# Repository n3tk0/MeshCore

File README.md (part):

> **This is a fork of [meshcore-dev/MeshCore](https://github.com/meshcore-dev/MeshCore).**
> It tracks upstream and adds a Faketec v5 companion build with its own encoder-driven UI (read and write messages without a phone), a mailbox and LoRa OTA updates for repeaters (with an Android app and an nRF52 bootloader that survives power cuts), light builds of any board, plus robustness fixes to the shared MeshCore code.
> Everything below "About MeshCore" is the upstream README. For general MeshCore support, issues and contributions, please use the upstream repository.

## 🍴 What this fork adds

- [Faketec v5 companion with encoder UI](#faketec-v5-companion-with-encoder-ui): hardware, wiring, controls, writing messages, settings, build flags
- [Repeater mailbox](#repeater-mailbox-store--forward-for-direct-messages): keeps direct messages for owners who are away
- [LoRa OTA for repeaters](#lora-ota-for-repeaters-nrf52-esp32): delta updates over the air from an Android app
- [Repeater battery from an INA219](#repeater-battery-from-an-ina219) and [repeaters that look after themselves](#repeaters-that-look-after-themselves): charge counting, battery saving steps (`battsave`), self test, telemetry history
- [nRF52 bootloader for LoRa OTA](#nrf52-bootloader-for-lora-ota): staged install that survives a power cut, rollback on boards with QSPI flash
- [Fixes to upstream MeshCore](#fixes-to-upstream-meshcore): crash and hang fixes that apply to every board
- [New shared components](#new-shared-components): reusable drivers and hooks added under `src/` and `examples/companion_radio/`
- [Builds and CI](#builds-and-ci)

> Status: the Faketec v5 firmware compiles and boots with BLE. The UI has been checked in the screen simulator (`tools/ui-sim`); the latest changes (network tools, channels from the device, learned words, hardware check, buttons instead of the encoder, repeat) have not been tested on hardware yet. The repeater mailbox, LoRa OTA and the bootloader pass their unit and host tests and build in CI, but have not been tested on hardware yet either; neither have the battery steps, self test, telemetry history and the app's Health and "Update several" pages.

### Faketec v5 companion with encoder UI

A companion radio build for a Faketec v5 (rev A) board without the on-board BMS/MOSFET, with a local screen and jog-dial controls so the node can be used without a phone. User manual in Bulgarian: [docs/faketec-companion.bg.md](./docs/faketec-companion.bg.md).

| Part | Used here |
|---|---|
| MCU | Nice!Nano v2 / nRF52840 Pro Micro clone |
| Radio | Heltec HT-RA62 (SX1262) |
| Display | 128x64 SSD1306 I2C OLED (e.g. WINSTAR WEA012864) |
| Encoder | Quadrature rotary encoder with push switch (e.g. ZIPPY AN-P1S-2SP-Z), or three buttons instead (see below) |
| Buttons | User button (Back) and reset; use 2-pin switches, a 4-pin switch shorts on the SW1/SW2 footprint |
| Haptics | 3 V coin vibration motor on the board's T2 MOSFET footprint (optional) |
| Power | 1S LiPo straight from the controller's charger, battery read through a divider |

**Wiring**

| Function | Pin |
|---|---|
| Encoder A / B | P1.01 / P1.02 (common to GND) |
| Encoder push | P1.07 |
| Buttons instead of the encoder | Up P1.01, Down P1.02, Enter P1.07 (each to GND) |
| User button (Back) | P1.00 |
| OLED SDA / SCL | P1.04 / P0.11 (board I2C) |
| Vibration motor | T2 gate = P0.08, motor between B+ and drain pad J7, flyback diode across the motor |

**Controls** (Sony Ericsson CMD-Z7 style jog dial, UI in [`examples/companion_radio/ui-encoder`](./examples/companion_radio/ui-encoder))

| Input | Action |
|---|---|
| Turn | Move in lists, scroll a conversation; on standby, next status card (summary, recently heard, radio, battery, GPS) |
| Press | Open / confirm; in a conversation, reply to the selected message |
| Hold press | Quick menu (advert nearby, advert to the whole mesh, transmit on/off, Bluetooth, GPS, power off) or the actions of the current item |
| Back (BTN) | Back one level; on standby, screen off |
| Hold Back | Standby from anywhere; on standby, lock the keys (hold Back again to unlock); while the boot splash shows, CLI rescue |
| Hold Back + press 2.5 s | Power off ("Power off" shows, a double buzz confirms; does nothing while the keys are locked). To switch on, hold Back + press together ~1.5 s until it buzzes; a shorter press goes back to sleep. With USB power it starts at once. In quiet mode neither buzzes |

**Messages**

- **Messages** lists conversations (contacts and channels), newest first, with the unread count or the age of the last message. A conversation opens as a chat: every message wrapped over as many rows as it needs, my messages with their delivery icon, the age of the selected one in the title. Press replies, hold opens Reply / Resend / Delete.
- **Channels** opens a channel's conversation (or the reply picker when it has none yet). Hold on a channel: write, mute (no buzz or screen wake, except for mentions; stored in `/ui_mute`) or delete. The last row, **+ Add**, joins a `#hashtag` channel typed on the keyboard (key = first 16 bytes of `sha256("#name")`, the same as the app).
- **Message details:** hold on a message > Details shows the time, the route (direct / flood / hops), SNR and RSSI of a received message, or the attempts and state of a sent one.
- **Reply** first asks **Quick reply** or **Write**. A quick reply can be sent as is or finished on the keyboard. Replies go to where the message came from (contact or channel).
- **Sending** waits 3 s with a progress bar; Back cancels it. Direct messages are tracked: a clock until the ACK, then a check mark. Without an ACK the message is sent again automatically with the same timestamp (the recipient shows it once), the last attempt as a flood; after 3 attempts it is marked not delivered with a long vibration, and **Resend** starts a new round. Channel messages have no ACK and show as sent.
- **Mentions:** a channel message with `@name` or `@[name]` for this node vibrates and wakes the screen like a direct message.
- **Recipient list:** channels (`#`) first, then chat and room contacts, sorted by name or by last heard. Sorted by name, a row of first letters sits on top: turn left from the first entry, press, turn to a letter, press to jump to the first name with it.
- **Keyboard:** BG, EN and 123 layouts with shift (automatic capital at the start and after `. ! ?`), space, language and send keys. Turn to pick a key, press to type, Back deletes, hold opens Send / Clear / Discard. An unsent message is kept for its recipient while you write elsewhere.
- **Next word:** after a space, the word you most often sent after the previous one is suggested (pairs learned from sent messages, up to 192, ~3.5 KB in `/ui_pairs`; punctuation breaks the chain; Settings > Messages > Learned words > Clear also clears them).
- **Word prediction:** the most frequent dictionary word for what you are typing is shown after the cursor and is selected right after each letter: **press** accepts it and adds a space, turning goes back to the keys. The dictionary (6000 Bulgarian + 4000 English words, ~71 KB flash) is chosen by the script you type in; words you typed recently are suggested first. It is generated by [`ui-encoder/tools/gen_dict.py`](./examples/companion_radio/ui-encoder/tools/gen_dict.py) from [FrequencyWords](https://github.com/hermitdave/FrequencyWords) (CC-BY-SA-4.0). Learned words: words you send that the dictionary lacks (names, places, slang; 3+ letters) are learned, up to 128, stored in `/ui_words`, and suggested before dictionary words.
- **Nothing is lost before the app syncs:** every message for the phone app is written to flash as it arrives (`-D OFFLINE_QUEUE_PERSIST`, an append-only log) and leaves it only when the app has fetched it, so it survives a reset, a hang or a flat battery (up to 256 messages; when full, the oldest channel messages go first). The device's own history (last 24) is not cleared by a sync; it is written within 10 minutes of a change, at power off and before an update. Messages sent from the device do not appear in the phone app's history.

- **Quiet hours:** Settings > Messages > Quiet hours (off, 22–07, 23–07, 00–07, 22–06, 23–06): in those hours channel messages neither wake the screen nor vibrate; direct messages and mentions still do. Only with a valid clock (from the app or an advert); without one it is off.
- **"I'm back":** after a power-on or a wake from sleep/hibernate, and when a repeater is heard again after 10+ minutes without one (its advert, or any flood packet it passes on, so a node that stays near a repeater does not do it every hour), the companion sends one zero-hop advert by itself (at most once in 10 minutes, only while transmit is on), so a repeater's mailbox hands over at once (`-D BACK_ADVERT`). When the mailbox delivers, the screen shows "Mailbox: N msgs".
- **Battery:** the battery card shows the voltage and the time left (e.g. `3.8V ~18h`), from how fast the percentage fell over the last hours; the next card is a 24-hour graph of the battery with its low–high %. The history (every 10 minutes for 24 h, every hour for a week, `-D TELEMETRY_HISTORY`) is kept in `/tele_hist` and the app reads it (BLE command 121).

**Network** (Menu > Network)

- **Nearby:** a zero-hop discover request; the repeaters that answer in 10 s, strongest first. A repeater shows how well it hears us (↑) and we hear it (↓), and starts a trace or range test to it. Hold searches again.
- **Trace:** from a contact (hold > Trace) or a nearby repeater: a TRACE packet there and back through the repeaters of its path, with the SNR at each hop and the round-trip time.
- **Airtime:** transmit time in the last hour against the EU 868 MHz 10% duty cycle, total TX time, packets sent / received / errors, noise floor, last SNR and RSSI.
- **Range test:** a trace to the chosen repeater or contact every 15 / 30 / 60 / 120 s, a buzz for each answer (a different one for a miss), the last results with SNR there and back. Keeps running with the screen off until stopped (an icon in the standby status row shows it); stops if transmit is switched off.

**Settings** (Menu > Settings, saved in prefs)

| Group | Settings |
|---|---|
| Display | menu font and text font size (large / medium / small / tiny), screen timeout (15 s – 5 min), brightness, page dots |
| Hardware | encoder direction, encoder steps per detent (2 / 4; hidden with buttons), vibration, keyboard jump to the likely next letter, key lock (by hand / automatic when the screen goes off), input test, vibration test, screen test, readings (battery raw/ADC, USB, reset reason, noise floor, uptime) |
| Messages | alerts (without phone / always / never), wake the screen for (direct and mentions / all / never), quiet hours, confirm deletes, contacts sort, 10 quick replies (stored in `/ui_quick`), learned words (count, clear) |
| Radio | transmit on/off, TX power, antenna question (after a new battery / every boot / never), preset (EU/UK Narrow, EU/UK Deprecated; anything else shows as custom), repeater |
| System | node name (an advert with the new name is offered; the Bluetooth name changes after a restart), language BG / EN, time zone, EU summer time, battery calibration, about, CLI rescue, firmware update over USB (UF2 drive) or BLE (DFU) |

**Buttons instead of the encoder:** Up on P1.01, Down on P1.02 and Enter on P1.07, each to GND. The firmware is the same: after a new battery, the first turn or press at the antenna question shows which is fitted, and that is remembered across restarts and power off. A held button repeats. A wrong guess fixes itself: two full encoder clicks in one direction within 1 s switch to the encoder, two presses of one button within 2 s switch to buttons.

**Repeater (emergency only):** Settings > Radio > Repeater (or the phone app) makes the companion repeat other nodes' packets. It loads the mesh and the battery, so it asks "Emergency only! Turn on?" first, and a tower icon shows in the status row while it is on. It is allowed on 433.000, 869.495, 869.618 (EU/UK Narrow) and 918.000 MHz (`-D ALLOWED_REPEAT_FREQ_RANGE` in the Faketec ini); while it is on, a preset on another frequency is refused.

**Battery calibration:** Settings > System > Battery shows the measured voltage; set it to what a multimeter shows at the battery and the divider factor is saved in prefs. The shown value is averaged, and the node powers off only after three low readings in a row, so a transmit pulse does not switch it off.

**Watchdog:** the nRF52 hardware watchdog (30 s, `-D WATCHDOG_SECONDS`) restarts a node whose main loop hangs, e.g. on a stuck I2C bus, so the low-battery cutoff keeps working. The bootloader feeds it, so DFU and UF2 updates are not affected.

**Build flags** (in [`variants/faketec_v5/platformio.ini`](./variants/faketec_v5/platformio.ini))

- `-D DISPLAY_CYRILLIC`: Cyrillic 5x8 font for the SSD1306.
- `-D PIN_VIBRATION`, `-D VIBRATION_PWM=190`: haptic patterns (key click, confirm, channel / direct message, power off); PWM keeps the motor near 3.1 V on a full LiPo. Remove to build without a motor.
- `-D AUTO_SHUTDOWN_MILLIVOLTS=3300`: there is no BMS, so the node hibernates below this voltage. Calibrate in Settings > System > Battery (or set `-D ADC_MULTIPLIER` for your divider).
- `-D ENCODER_STEPS_PER_DETENT=2`, `-D ENCODER_REVERSE=true`: build defaults for the encoder; both can also be changed in Settings.
- `-D DISABLE_RTC_AUTODISCOVERY`, `-D DISABLE_ENV_SENSORS`: skip the RTC probes and the sensor scan when none are fitted (a faster boot; a bad I2C bus no longer hangs it, see below).
- `-D ALLOWED_REPEAT_FREQ_RANGE=...`: the frequencies where the repeater setting may be turned on (upstream allows 433.000, 869.495 and 918.000 MHz; this build adds 869.618).

Build with PlatformIO, e.g. `pio run -e Faketec_v5_companion_radio_ble` (or `_usb`), then flash the UF2 by double-tapping reset and copying it to the bootloader drive.

<!-- release-notes:repeater:start (tools/repeater-release-notes.sh puts the text from here to the end marker in the repeater release) -->
### Repeater mailbox (store & forward for direct messages)

Every repeater built from this fork (`-D NO_MAILBOX` leaves it out) can keep direct messages for up to 4 owner companions while they are away, and hand them over when the owner is heard again with no hop between. Nothing is flooded: messages are kept from traffic the repeater hears anyway, and handed over as zero-hop packets that nobody repeats.

- **What is kept:** only `TXT_MSG` packets addressed to an owner (by the first public key byte, the only one in the packet), still encrypted to the owner; the repeater cannot read them. Channel messages, adverts and messages sent with no hop (the owner is next to the sender, or another mailbox is handing over) are not kept. Off until `mailbox learn` or `mailbox on`. Up to 64 messages (8 on STM32) in flash (`/mailbox`), so they survive a restart; older than `ttl` hours are dropped (after a restart without a clock, the age counts from the restart); when full, the oldest goes.
- **Only while away:** an owner heard with no hop in the last `away` minutes (its signed advert, or its ACK to a message this mailbox handed over; a packet that only carries the first key byte does not count, since a neighbour may share it) is present, and nothing is kept for it. A flood message the owner answered with a PATH reply in the next 2 minutes is dropped as delivered. A sender's automatic retries (same sender, same length, within 30 s) are kept once.
- **Hand-over:** on any zero-hop packet from the owner (an advert, a message, a request, a PATH; the Faketec sends an advert by itself when it comes back), the kept messages go out one every 2.5 s as zero-hop direct packets. A packet other than an advert carries only the first key byte, which other nodes can share, so then one message goes at a time and the next only after the owner's ACK was heard (at most one such try a minute); a signed advert arriving meanwhile lets the rest go without waiting; only an ACK sent to this repeater counts. If the owner's ACK goes out through another repeater, this one does not hear it: the message stays and goes again with the owner's next packet, and the companion shows it once (a repeat, never a loss). The owner ACKs them as usual; a sender that is still on the mesh gets the late ACK, and the Faketec UI turns its "not delivered" into delivered.
- **Shown once:** the companion firmware drops a direct message it already showed (same sender and timestamp, last 32), so a kept copy or a retry is not shown twice; the sender still gets its ACK.
- **Count:** the number of kept messages is in `selftest` (`mail=N`) and on the app's Health page.
- **CLI** (serial or remote admin): `mailbox` (state), `mailbox on|off`, `mailbox learn` (the next companion advert with no hop in 2 minutes becomes an owner), `mailbox add <64-hex key>`, `mailbox del <key prefix>`, `mailbox list`, `mailbox ttl <hours>` (default 72), `mailbox away <minutes>` (default 10), `mailbox clear`.
- **App:** the Android app's Mailbox card (repeater Tools) shows the recipients by contact name, adds the connected companion with one tap ("Add me", its own key, no advert needed), a contact or a pasted key, and changes on/off, `ttl`, `away`; the repeater lists show ✉ N ("you too") from the last read.

### LoRa OTA for repeaters (nRF52, ESP32)

- **How:** the Android app in [`android/`](./android) (user guide with screenshots in Bulgarian: [docs/android-app.bg.md](./docs/android-app.bg.md)) makes a delta from the firmware the repeater runs to the new one and sends it through your companion, only with no hop, on a side channel (default 869.470 MHz / 125 kHz / SF7) so the main channel keeps working.
- **Off by default:** run `set ota on` in the repeater's console first (`set ota off` turns it off again, `ota status` shows it). `ota sha` prints the SHA-256 and size of the running image (kept in `/ota_sha`, so it is hashed once per build); the app finds the matching firmware in the releases with it, and the commit in the ident (`<version> <date> <commit>|<board>`) tells which build it is.
- **Cut short:** the repeater goes back to its normal channel and keeps its progress for 30 minutes; the same update in the app continues where it stopped.
- **Time on air:** the app keeps to 10 % of each hour; a bigger delta waits for the next part of the hour on the normal channel.
- **nRF52 storage:** the new image goes to the free internal flash after the running one, then is copied over it just before the restart. Repeaters with a QSPI flash (Xiao nRF52840, Ikoka Stick/Nano/Handheld, T-Echo, ThinkNode M1/M6, Wio Tracker L1 and L1 1W, SenseCAP Solar; `-D QSPI_STORAGE`) keep it there instead, together with the mailbox (a ring of 24 slots) and a copy of the running image for rollback (832 KB each, more than the whole app area). Boards where the old and the new image do not fit together (e.g. RAK4631, about 460 KB) update **in place**: the repeater keeps the delta and the end of the image, and makes the start again in RAM just before the copy. The app shows a big warning for it.
- **Our bootloader (nRF52):** with [our bootloader](#nrf52-bootloader-for-lora-ota) the final copy survives a power cut, and boards with QSPI flash get rollback.
- **Power cut on nRF52 without it:** during the final copy (about 20 s) a power cut leaves the repeater in the bootloader with no firmware; it has to be updated on site (USB or BLE DFU). The stock bootloader then at least checks the image's CRC at every start. ESP32 has two app slots and is not at risk.
- **Low battery:** the final copy waits while the repeater runs on a battery below 3.7 V (`-D OTA_MIN_BATT_MV`); the update is paused and the app offers to continue.
- **Watchdog on nRF52 repeaters:** 60 s (`-D REPEATER_WATCHDOG_SECS`, 0 = off). It cannot be stopped: after loading firmware that does not feed it, press RST once.
- **New firmware must prove its radio:** a new image (ESP32, or nRF52 with rollback) is confirmed by an admin login, or once it has sent and received a packet within 10 minutes (it sends an advert at 5 minutes if it has not sent anything). With nothing heard by 60 minutes it is still confirmed when its noise floor is sane (-140..-60 dBm, a quiet area), otherwise it rolls back. `ota rollback` does it by hand.
- **Where the firmware comes from:** the app offers three sources for both an update over LoRa and a flash over Bluetooth / Wi-Fi: **Releases** (ours with `ota-manifest.json`, and for a flash also stock MeshCore from meshcore-dev), **New build** (runs [Build Firmware for Boards](#builds-and-ci) on GitHub with the board picked from the device and the workflow's own boxes, then downloads the run's artifact and checks it against its `.ota.json`) and **File**. A build needs a fine-grained GitHub token for this repository with *Actions: Read and write* and *Contents: Read*; it is kept on the phone only, encrypted with an Android Keystore key. The app follows the run in the background and notifies when it is done. For a group: Actions > Build LoRa OTA Android App > Run workflow with *group APK* builds a second APK with the token from the secret `LORAOTA_GITHUB_TOKEN` (XOR-ed, not readable as text, but anyone who takes the APK apart can get it), only as an artifact kept 3 days, never in a release.
- **Flash from a file:** `.zip` (DFU package), `.bin` (Wi-Fi, ESP32) or `.uf2`; a `.uf2` is turned into a DFU `.zip` in the app (application only, any SoftDevice), so the same file as for the USB drive works over Bluetooth. A bootloader or SoftDevice `.uf2` is refused.
- **Bluetooth flash log:** the flash screen shows the DFU library's log while it runs and keeps it after an error, with a Copy button. A repeater is flashed without a bond and the app looks for its bootloader by scanning (the Adafruit bootloader advertises on the address + 1 after a jump from the app).
- **4-tab repeater workspace (`Overview` · `Health` · `Firmware` · `Tools`):**
  - **Overview:** battery status (with chemistry selection and INA219/BQ25798 current), **Quick Actions** (1-tap UTC clock sync from the phone, flood advert, refresh, reboot confirmation, and a **5x Ping Link Range Test** reporting delivery % and min/avg/max RTT ms), and **Neighbors** (resolves 8-hex prefixes to contact names, shows color-coded SNR badges, supports `neighbor.remove`, and calculates **Haversine distance & compass bearing** such as `14.2 km SE (138°)` when coordinates are known).
  - **Health:** summary card, `selftest` in words, lazy on-demand 24 h / week telemetry charts with **CSV export**, past checks, and collapsible `battsave` / battery capacity configuration.
  - **Firmware:** LoRa delta OTA and Bluetooth DFU / Wi-Fi OTA with a sticky bottom action bar.
  - **Tools:** interactive **CLI console** (also available locally for the companion; supports quick chips, custom persistent snippets with secret-command blocking, history, `get`/`set` autocomplete, RTT badges, dangerous-command confirmation, stock companion fire-and-forget mode, and redacted copy/share), **Visual Settings Editor** (writes only modified keys, validates ranges, fills `lat`/`lon` from **phone GPS** in 1 tap, supports **reusable Config Profiles**, and embeds a **live LoRa Airtime / Bitrate / Sensitivity / 10% duty-cycle calculator**), safe temporary radio test (**`tempradio`** with auto-revert), and Backup / Restore.
- **Fleet management & Batch Health Sweep:** pin important repeaters to the top, filter by `All | Direct | Issues | Pinned`, see latest battery % and health status dots in the repeater list, and run **Fleet Health Sweep** to sequentially log in to selected repeaters, run `selftest` (with optional batch UTC clock sync), store results, retry failed nodes, and share a text report.
- **4-tab Offline Hub (`Health` · `Backups` · `Firmware` · `Audit & Mesh`):** works without a Bluetooth connection:
  - **Health & Backups:** search saved health checks and backups, **import external `.json` backup files**, **compare any two backups (Diff)**, or save a repeater backup as a reusable config profile.
  - **Offline Firmware Hub:** pre-cache release firmwares (`Prepare for field` board picker with search and role filters), trigger custom GitHub builds for **any device role (`Repeater`, `Companion`, or `Room server`)**, export `.bin` / DFU `.zip` files, or **Flash directly (`Flash`)** over BLE DFU (`*_OTA` / `DfuTarg`) or ESP32 Wi-Fi (`MeshCore-OTA`) in the field without a companion.
  - **Audit & Mesh Intelligence:** inspects **Offline LoRa OTA Delta Readiness** (whether both base and target `.bin` files are cached for each known repeater), runs an **Automated Fleet Configuration & Security Audit** (radio mismatch, `lat=0, lon=0`, `repeat=off`, open guest write access, low battery), and builds a **Mesh Link Topology & SNR Asymmetry Matrix** flagging bidirectional links with `>= 6.0 dB` asymmetry.
- **Security, BLE Auto-Reconnect & Full Workspace Archive:** repeater admin passwords are encrypted with Android Keystore AES/GCM (`PasswordStore`); unexpected BLE disconnects automatically retry twice before dropping the session; `Settings` includes in-app GitHub self-update (`AppUpdater`), redacted diagnostic report sharing, and **Encrypted Full Workspace Archive** export/import (`PBKDF2-HMAC-SHA256` + `AES-256-GCM`) bundling all backups, health history, repeater passwords, pins, CLI snippets, config profiles, and observed neighbor topology.
- **Several repeaters at once:** "Update several repeaters" picks a release and the repeaters with a kept password (the others are shown greyed: log in to them once; those with hops are marked as skipped unless the route becomes direct). A confirmation lists the repeaters and the release. It then logs in, backs up and updates them one after another (no-hop routes first), keeps to the shared airtime limit, saves the queue after each one so it goes on after an interruption, keeps running with the screen off (one notification for the whole queue), marks a repeater that fails (a broken download, an odd answer) and goes on with the next (only a lost companion stops it), and ends with a report (updated / already up to date / skipped and why / failed). A repeater that needs an in-place copy is skipped (do it by hand).
- **APK signing:** CI signs with the key from the secrets `LORAOTA_KEYSTORE_BASE64`, `LORAOTA_KEYSTORE_PASSWORD`, `LORAOTA_KEY_ALIAS`, `LORAOTA_KEY_PASSWORD` (a debug key when they are not set).

### Repeater battery from an INA219

With an INA219 in the battery line (the battery on Vin+, the load and the charger on Vin-), the repeater takes the battery from it instead of the board's ADC: bus voltage plus the drop over the shunt. It is used in the status, telemetry channel 1, the `power` command and the battery check before a LoRa OTA install. The INA219 channel also carries the current with its sign as an analog input (Cayenne LPP current has no sign): negative while charging, positive while discharging. Without an INA219, or after it was turned off for I2C errors (see `i2c` below), the board's own reading is used.

### INA226 battery and the xiao-solar-lite v0.6 board

An INA226 at 0x44 is plain telemetry on every board. With `-D INA226_BATTERY=1` it is the battery, like the INA219 above (battery on Vin+, load and charger on Vin-, 100 mOhm shunt): the voltage, the charge counting and the percentage in telemetry come from it, the board's ADC is not used, and when a read fails or the sensor is turned off the last good value is kept (unknown, 0, until the first good read; `battsave` and the OTA check treat that as no reading). A second INA226 at 0x45 (found by its manufacturer ID) is a second telemetry channel. `-D INA226_LOW_POWER=1` reads them in triggered mode with 16 averages (~35 ms, the chip rests at ~2 uA in between).

`Xiao_nrf52_solar_repeater` is one XIAO nRF52840 + Wio-SX1262 repeater for every XIAO solar board, found at boot (`solar` command: BQ25798 lite v0.5, CN3791 lite v0.6, MSPM0 xiao-solar / smart-mppt; `Xiao_nrf52_solar_lite_repeater` is the same build under the old name). On the CN3791 (former ultralite) board: a CN3791 buck MPPT charger, the battery INA226 on 0x44 and the solar input INA226 on 0x45 (SCL D6 / SDA D7); the XIAO's own battery pad is not connected. D0 drives the charger's panel voltage set-point through a PWM (`-D SOLAR_MPPT_PWM_PIN=D0`); `charger` takes the same words as on a BQ25798 (`vin mppt|off|<mV>`, `ichg` 100..600 mA as a software limit through the set-point, `scan`, `cutoff` = the battsave off step; `mppt` is short for `charger vin`), see the [docs](./docs/cli_commands.md#solar-panel-set-point---mppt-repeater-xiao-solar-lite-v06). Not hardware-tested yet.

### xiao-solar-lite charger (BQ25798)

All solar boards (commands and capabilities per board and version): [docs/solar-boards.bg.md](./docs/solar-boards.bg.md).

`Xiao_nrf52_solar_lite_repeater` is the XIAO nRF52840 + Wio-SX1262 repeater for the xiao-solar-lite board (a small BQ25798 solar charger for XIAO + Wio-SX1262; private repo Meshcore-hardware): BQ25798 on I2C (0x6B, SCL D6 / SDA D7), its ~CE on D0 (so D0 is no button here). The firmware turns the charger's watchdog off and keeps its setup (Li-ion 4.20 V or LiFePO4 3.60 V, 1 A, MPPT on again every morning, TS ignored unless an NTC is fitted, ship FET), reads battery and panel voltage and current from the charger's ADC every 10 s for status, telemetry, charge counting and `battsave`, and puts the board into shutdown mode when the battery is empty and there is no sun (only the panel wakes it). `charger` in the CLI ([docs](./docs/cli_commands.md#charger---bq25798-on-xiao-solar-lite-repeater-only-xiao_nrf52_solar_lite_repeater)). The XIAO ESP32-C3 is not supported on this board (D0 is a strapping pin there). Not hardware-tested yet.

### Repeaters that look after themselves

- **Charge counting (INA219):** with the current sensor the repeater counts the charge in and out: a real %, hours left at the 6-hour average, and today's / yesterday's mAh in and out. The capacity is learnt from a full charge (4.15 V with only a trickle going in) down to empty (3.3 V), or set with `battery capacity <mAh>`. In telemetry, `selftest` and `battery`.
- **Power steps:** below 3.6 V adverts go half as often and the mailbox stops writing to flash; below 3.45 V no LoRa OTA and no mailbox; the 'off' step (radio off, only battery checks: ESP32 deep sleep 30 min and back to sleep at once on waking if the battery is still under off + 150 mV; nRF52 every 10 min) is not on by default, because a wrongly calibrated ADC would take a remote repeater off the air; `battsave 3600 3450 3300` (or the app's battery card) turns it on. It restarts the node when the battery is 150 mV above it or on external power; an ESP32 woken by its timer checks the battery before the radio starts (with an INA219, right after the sensors, and puts the radio back to sleep) and sleeps again while it is still low. 3 readings in a row decide a step down, 100 mV above the limit a step up. `battsave` shows and sets it. It is not upstream's `powersaving` (the MCU sleeps between packets while the radio listens); both can be on.
- **Sensors come back:** a sensor turned off after I2C errors is tried again after 10 minutes, 1 hour, then every 6 hours (after a day without errors a new drop-out starts again from 10 minutes), and set up again when it answers (a lost supply resets its registers); `i2c` shows how often it dropped out.
- **Self test:** `selftest` gives one line for the app's Health page and for people (see [docs](./docs/cli_commands.md#self-test)).
- **Telemetry history:** every 10 minutes for 24 h and every hour for a week (battery, current, temperature, humidity, pressure, noise, packets, airtime), kept in `/tele_hist` (saved every hour), read by the app with request `0x41` (not on STM32); each reply also says which values the node has, so the app offers only those, and a value it does not measure costs one short reply. After a restart without a clock the time goes on from the last known one (the time the node was off shows as a gap once the clock is set).

### nRF52 bootloader for LoRa OTA

[`bootloader/`](./bootloader) is the [OTAFIX bootloader](https://github.com/oltaco/Adafruit_nRF52_Bootloader_OTAFIX) (pinned commit) with one addition, a **staged install**. Details, layout and build: [bootloader/README.md](./bootloader/README.md).

- **What it changes:** the repeater puts the whole new image where the copy does not touch it (the QSPI flash, or the internal flash after the running image), writes a small record in the bootloader settings page and restarts. The bootloader checks the image (CRC-32), copies it, checks the result and marks the record. The source is never written, so a power cut during the copy only makes it start again.
- **Rollback (boards with QSPI flash):** the running image is also kept in the QSPI flash and the new one runs on trial. It is confirmed by an admin login, an INFO from the LoRa OTA app or 10 minutes of uptime; after 3 restarts without that (a crash, or a hang caught by the watchdog) the bootloader copies the old image back. `ota rollback` on the repeater does it by hand.
- **Old bootloader:** firmware from this fork still updates the old way (RAM copy), and now also stores the image's CRC16, which the stock bootloader checks at every start.

| What a repeater gets | Boards |
|---|---|
| staged install + rollback (`-D QSPI_STORAGE` in the repeater env) | Xiao nRF52840, Ikoka Stick / Nano / Handheld (Xiao bootloader), LilyGo T-Echo, ThinkNode M1, ThinkNode M6, Wio Tracker L1 and L1 1W, SenseCAP Solar P1 |
| staged install, normal build (image up to 396 KB) | ProMicro / Faketec, T1000-E, ThinkNode M3, Heltec T114 without display, RAK WisMesh Tag, Minewsemi ME25LS01 |
| staged install only with a light build (`build-boards.yml`, about 310-336 KB) | RAK4631, RAK3401, Heltec T114 with display, Heltec T096, Heltec T1 |

Every repeater board and which bootloader it should use (and why the others keep the stock one): [bootloader/README.md](./bootloader/README.md#every-repeater-board). Bigger images still update over LoRa, the old way. T114 and T1000-E have QSPI flash, but its pins are not known yet; RAK boards have at most 1 MB of QSPI flash, too small for the layout.

**Install** (once per node): get `update-<board>_bootloader-…-mcota1_nosd.uf2` from a `bootloader-v*` release or the Build Bootloader workflow's artifacts, double-tap RST and copy it to the drive. `INFO_UF2.TXT` on the drive names your board; on a Xiao pick the Sense file only if it says `SeeedXiaoSense`. The firmware finds the new bootloader by itself; nothing else needs changing.

### Fixes to upstream MeshCore

These are in shared code and apply to every board.

- **Crash on short frames from the app:** `CMD_SEND_CHANNEL_TXT_MSG` shorter than its 7-byte header made the text length negative and `sendGroupMessage()` copied ~4 GB. All command handlers that read fixed-size fields now check the frame length first, instead of reading stale bytes from the previous frame; `REBOOT` / `FACTORY_RESET` could previously match text left over from an earlier frame. `SEND_RAW_DATA` path length and `SET_DEFAULT_FLOOD_SCOPE` name scan are bounded.
- **Malformed radio packets:** a `PAYLOAD_TYPE_PATH` whose path runs past the data no longer underflows the extra length and overruns `out_frame`; `TRACE` packets need tag, auth and flags before the hop offset is computed; contact responses are clamped to the frame size.
- **Invalid path lengths:** an invalid `out_path_len` from the app or from `/contacts3` is treated as unknown (flood) instead of producing malformed direct packets.
- **nRF52 BLE RX race:** the RX queue was shifted in `loop()` while the Bluefruit callback appended to it without locking, so frames could be lost or duplicated. It is now a single-producer / single-consumer ring; connect / disconnect request a flush that `loop()` performs.
- **Atomic saves on nRF52:** contacts, channels and prefs are written to a temp file and renamed, so a reset or brown-out during a save no longer corrupts them (falls back to an in-place write when the filesystem has no room for a second copy).
- **Hang on the I2C bus (nRF52):** the Adafruit Wire driver waits on the TWIM with no timeout and reads an error left by an earlier transfer as its own, so a loose cable or a module holding a line could stop a node at boot or in a sensor read. [`arch/nrf52/libs/nrf52_wire`](./arch/nrf52/libs/nrf52_wire) is that driver with a 50 ms timeout on every wait (`-D WIRE_TIMEOUT_MS`), a reset of the TWIM, bus recovery (9 SCL clocks and a STOP), stale events cleared before each transfer and error counters; it replaces the framework's Wire on every nRF52 build, so sensor libraries and displays get the timeouts too. A device that times out at boot, or whose reads fail 3 times in a row, is turned off until a reboot and the others go on (it keeps its telemetry channel). The CLI command `i2c` lists what was found and what was turned off and why ([docs](./docs/cli_commands.md#show-the-i2c-devices-and-the-ones-turned-off)). The flags `-D DISABLE_RTC_AUTODISCOVERY` and `-D DISABLE_ENV_SENSORS` still skip the RTC probes and the sensor scan.
- **Display left on after power-off:** `ui-new` and `ui-tiny` put a non-e-ink display to sleep before SYSTEMOFF, so the OLED no longer drains the battery after hibernate or low-battery shutdown.
- **STM32 builds:** `[stm32_base]` pins the STM32duino framework, because the new 3.0 release breaks RadioLib's Arduino HAL and drops `ltoa()`.

<!-- release-notes:repeater:end -->
### New shared components

- `src/helpers/ui/QuadratureRotaryInput`: interrupt-driven quadrature decoder with 2 or 4 transitions per detent, resync at the rest position, runtime direction and steps; ISR-safe on ESP32.
- `src/helpers/ui/SSD1306Display` + `CyrillicFont5x8.h`: UTF-8 Cyrillic rendering (`-D DISPLAY_CYRILLIC`); characters the font cannot draw show as a block.
- `src/helpers/ui/GenericVibration`: PWM drive and multi-pulse patterns.
- `src/helpers/ui/MomentaryButton::setDebounce()`: debounce without the multi-click delay, so presses register at once.
- `AbstractUITask::msgSource()`: optional hook telling a UI whether the next message came from a contact or a channel (no-op for the other UIs).
- `DataStore::loadSmallFile()` / `saveSmallFile()`: small UI-owned files with the same atomic save.
- `src/helpers/I2CHealth`: I2C probe with a timeout result, the error counters and the list `i2c` shows.
- `SensorManager::getBatteryMilliVolts()`: a battery from a sensor (the INA219), 0 when there is none.

### Builds and CI

- [`.github/workflows/build-boards.yml`](./.github/workflows/build-boards.yml) builds chosen boards by hand (Actions > Build Firmware for Boards > Run workflow): pick a repeater / companion / room server from the drop-downs, type more env names, or add a whole group (a filter such as `Xiao` narrows only the group; picked boards are always built). Light by default: RTC, sensors, GPS, screen driver and debug logs stay out unless ticked (without the display box the screen is a no-op but buttons, LED and buzzer keep working; boards that start their GPS in their own code keep it) (mailbox and LoRa OTA stay in unless unticked), and such files get `-lite` after the board name; [`tools/lite-flags.sh`](./tools/lite-flags.sh) gives the same flags for a local build (a board with a sensor built in marks it in its env `build_flags`, e.g. `-D LITE_KEEP_INA260 -D LITE_KEEP_MLX90614`: that sensor is never dropped and the I2C scan stays on; `ENV_INCLUDE_BQ25798` counts too). After new boards arrive, `bash tools/gen-board-choices.sh` refreshes the drop-downs. Files go to the run's artifacts, and optionally to a GitHub pre-release. The LoRa OTA app can start it too (input `request_id`, which names the run so the app finds it).
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
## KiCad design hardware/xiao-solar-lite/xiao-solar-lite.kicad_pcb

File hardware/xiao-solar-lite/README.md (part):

# xiao-solar-lite: solar charger layer for XIAO + Wio-SX1262

The power part of [`../xiao-solar`](../xiao-solar) as the third layer of the standard
XIAO nRF52840 + Wio-SX1262 sandwich: this board at the bottom, Wio in the middle, XIAO on top
(USB and buttons stay reachable). Solar input, BQ25798 MPPT buck-boost charger, optional NTC,
ship FET, and DW01A + HJ8205 battery protection (BMS).
25 × 70.3 mm, 2 layers, all SMD parts on the top side (JLC assembly), no mounting holes.

The stack sits over the 14 XIAO holes at the USB end; since v0.5 nothing at all is under it (no SMD part inside the U3 outline, only tracks and vias): the
charger, the ideal diode and the BMS sit below the stack, 3 mm or more away from the header pins. Long pin headers go through all three boards.

Status v0.5: schematic, routed PCB, Gerber, JLC BOM/CPL. Not built or tested.

v0.3 (review 2026-10-29): charger zone redone after the BQ25798 layout guide (SLUSDV2C 8.4.1):
PMID, SYS, VBUS and BAT are copper areas, SW1/SW2 run short and wide to the inductor, the 100 nF
PMID/SYS caps sit at the pins, BTST/REGN/GND leave through vias under the package. Cap counts as
TI recommends (VBUS 2, PMID 3, SYS 5, BAT 2 × 10 µF), so the board grew by 4 mm. Small parts get
thermal spokes to GND (easier hand rework), the charger power caps stay solid.
Every layer change on a power net has two vias (no single-via hot spot), and no via sits in a pad.

v0.4 (2026-10-30, Argon review + v0.4 proposals, shared with the main board):
- Charger per TI 8.4.1: 0402 100 nF right over the PMID–GND(27) and SYS–GND(27) pins on top,
  SW1/SW2 drop through 3 vias each under the IC to short B.Cu copper to L1, pin 27 to several vias.
  L1 is a molded **MWSA0402S-2R2MT** (Isat 4 A, DCR ≤ 58 mΩ, less stray field near the radio).
- **JP3** solder jumper across the ship FET Q2: closed = no ship FET, for LiFePO4 (with the ship
  FET the BQ25798 starts above 3.40 V and stops below 3.20 V; without it 2.6 / 2.4 V).
- **DW01A + HJ8205 BMS** (`U2`, `Q3`, `R9`, `R10`, `C19`) on the low side of the battery, matching
  the main board (`2.4 V / 4.3 V` backup protection).
- **Optional NTC** (`J3` + `R2/R3 = 5.1k/30k`), matching the main board: firmware sets `TS_IGNORE`
  by default when no NTC is fitted; CLI command enables the 0–60 °C NTC window.
- D5 was an **LM66100** ideal diode (~30 mV drop instead of ~0.3 V), replaced in v0.5 (see below); D1 is **SS54**.
- DFM: no vias in SMD courtyards except the tented ones under U1, 4 mm GND via grid + 3 mm edge
  fence, GND vias at caps and signal vias, B.Cu kept whole under the charger, teardrops,
  3 fiducials, test points VBUS/PMID/SYS/BAT/GND/3V3/SCL/SDA, parts ≥ 1 mm from the edge,
  silk ≥ 0.8 mm without overlaps (some refs in tight spots are hidden, they stay on F.Fab).
- Rotations in the CPL: U1, U2, Q2, D1, D3, D4 agree with JLC's footprints. Q3 (+270, the HJ8205 has its
  pins in two columns in JLC's footprint) and the SOT-23 parts (+180) are confirmed by JLC's DFM view
  (2026-11-13); D5 is gone.

v0.5 (2026-11-13):
- **Discrete ideal diode instead of the LM66100** (same circuit as the xiao-solar main board, no extended-part
  fee): `Q5` AO3401A (C15127) in the SYS to VOUT path, mirror `Q6` / `Q7` MMBT3906 (C7420354),
  `R30` 1M and `R31` 470k (0603, C22935 / C23178). Q5, Q6, Q7, R30, R31 and C20 sit in one column
  right of the SYS caps (x = 22.2 mm, y = 38 to 57 mm); SYS reaches the Q5 drain over a short 0.8 mm stub,
  VOUT leaves the source on a 0.8 mm track along the right edge to U3 pin 14 (about 45 mm). The
  mirror lines are hand-routed 0.25 mm tracks on F.Cu, no vias.
- **All SMD pads are at least 3.0 mm (copper to copper) from every pin of the headers** (U3, J1, J3, J4, J5),
  as JLC's DFM asked on the main board, and **nothing is under the XIAO / Wio stack** (no courtyard overlaps
  U3). The board is now **25 × 65 mm** (was 23 × 62; later 66.3 mm for the connector row, see below): the extra 2 mm of width hold the ideal diode column,
  R11 / R12 (I2C pull-ups, right of the charger top) and the VOUT track; the stack sits against the left edge
  (U3 pins at x = 3.9 and 19.1 mm). The charger cluster moved down 0.7 mm, the bottom group (input diodes,
  BMS) 0.9 mm, the connector row to 3 mm from the bottom edge, R2 / R3 1.0 mm to the right and JP3 turned
  by 180 degrees.
- C9 is the basic C307331 (100n/50V 0402).
- **Connector row for JST XH 2.5 mm plugs (soldered into the 2.54 mm holes), board 25 × 66.3 mm** (was 65 mm):
  J1 SOLAR and J4 BAT are turned vertical (pins one above the other) at the edges, J5 I2C stays a horizontal row in
  the middle. J1: pins at x = 2.40, y = 61.30 (SOLAR_IN +) and 63.84 (GND). J4: x = 22.60, y = 61.30 (BATT+) and
  63.84 (BATT-). J5: x = 8.69, 11.23, 13.77, 16.31 at y = 63.84 (SCL SDA 3V3 GND). An XH body is modelled as 2.45 mm
  beyond the outer pins along the row and 2.35 / 3.40 mm across it: J1 body x 0.05 to 5.80, y 58.85 to 66.29;
  J5 x 6.24 to 18.76, y 60.44 to 66.19; J4 x 19.20 to 24.95, y 58.85 to 66.29. They are 0.44 mm apart, inside the
  board, and free of SMD parts. The two upper pins sit 3 mm from D1 and R30 (the length grew by 1.3 mm for that).
- Panel: 4 boards on 100 × 76.3 mm (the longer board adds 1.3 mm to the 75 mm height; the current mouse-bite panel is 106 × 84.3 mm, see Panel below).
- **Silkscreen:** JP2 is labelled `CHEM` (left of the jumper), `Li` over pad 1 (GND side, bridged 1-2 by default)
  and `LFP` over pad 3 (3V3 side); JP3 is labelled `LFP:short` (close only for LiFePO4). The I2C pin names sit under
  the J5 pins, all silk strokes are 0.15 mm and the U3 pin names 0.8 mm. These labels are added by
  `silk_fixups()` in `tools/gen_pcb.py`; on an already routed board `python3 tools/run.py silk_fix` applies them
  (once) without touching copper.
- **Stand-alone use (v0.5 update, board 25 × 70.3 mm, panel 106 × 84.3 mm)**: the board can run without our firmware.
  `JP4` (closed by default) is a 2-pad solder jumper in series between XIAO D0 (net `XIAO_D0`) and the BQ25798 CE net;
  cutting it leaves CE on `JP2` / `R4` only. `R32` (10k 0402, C25744, assembled) and `JP5` (open) form a fake NTC from TS to GND.
  JP3's label is now `LFP/SA:short` (SA = stand-alone). The three parts sit on the left edge between J3 and D3 (JP4 at
  x = 3.2, y = 47.8; R32 at 2.2, 50.6; JP5 at 5.8, 50.6, top side, 3 mm or more from the J3 pins), so the bottom group
  (D3, D1, BMS) moved 4 mm down (DB = 4.9) and the connector row with it: J1 pins at x = 2.40, y = 65.30 / 67.84, J4 at
  x = 22.60, y = 65.30 / 67.84, J5 at y = 67.84 (the XH body outlines are the ones above, shifted 4 mm down). JP4 / JP5 are not
  in the JLC BOM/CPL (solder them closed or cut them by hand). Labels: `cut` (JP4), `noNTC:short` (JP5). See
  "Stand-alone" below.
- Hand patches on the routed board that `gen_pcb.py` does not reproduce (re-apply them after `route` / `finish`):
  the locked REGN stub on B.Cu (10.55, 32.3) to (8.5, 32.3) is cut to end at 9.12 and split at 9.53 so that it joins
  the router's tracks, and the locked SCL stub on F.Cu (8.0, 34.1) to (6.4, 35.7) is shortened to end at (7.105, 34.995),
  both to remove `track_dangling` warnings (in the 70.3 mm run only the REGN stub needed it: it now ends at 9.51).
  Also by hand in the 70.3 mm run: the `NTC_FAKE` track R32 to JP5 pad 1 (a straight 0.25 mm track at y = 50.6, the router had
  looped around JP5), a solid GND connection of the `TP7` pad, and an extra `finish` rerun to clear GND islands. BATP (R8 to charger pin 18) is hand routed in `gen_pcb.py`
  (not a patch). Re-running `route` / `finish` can also leave one GND island or open pad that needs a via (see the
  gndfix / patch_route docs); Freerouting is not repeatable, so a rerun may need several tries.

## Stand-alone (без нашия фърмуер)
Use the board without our XIAO firmware (no I2C traffic, XIAO running something else or absent):
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
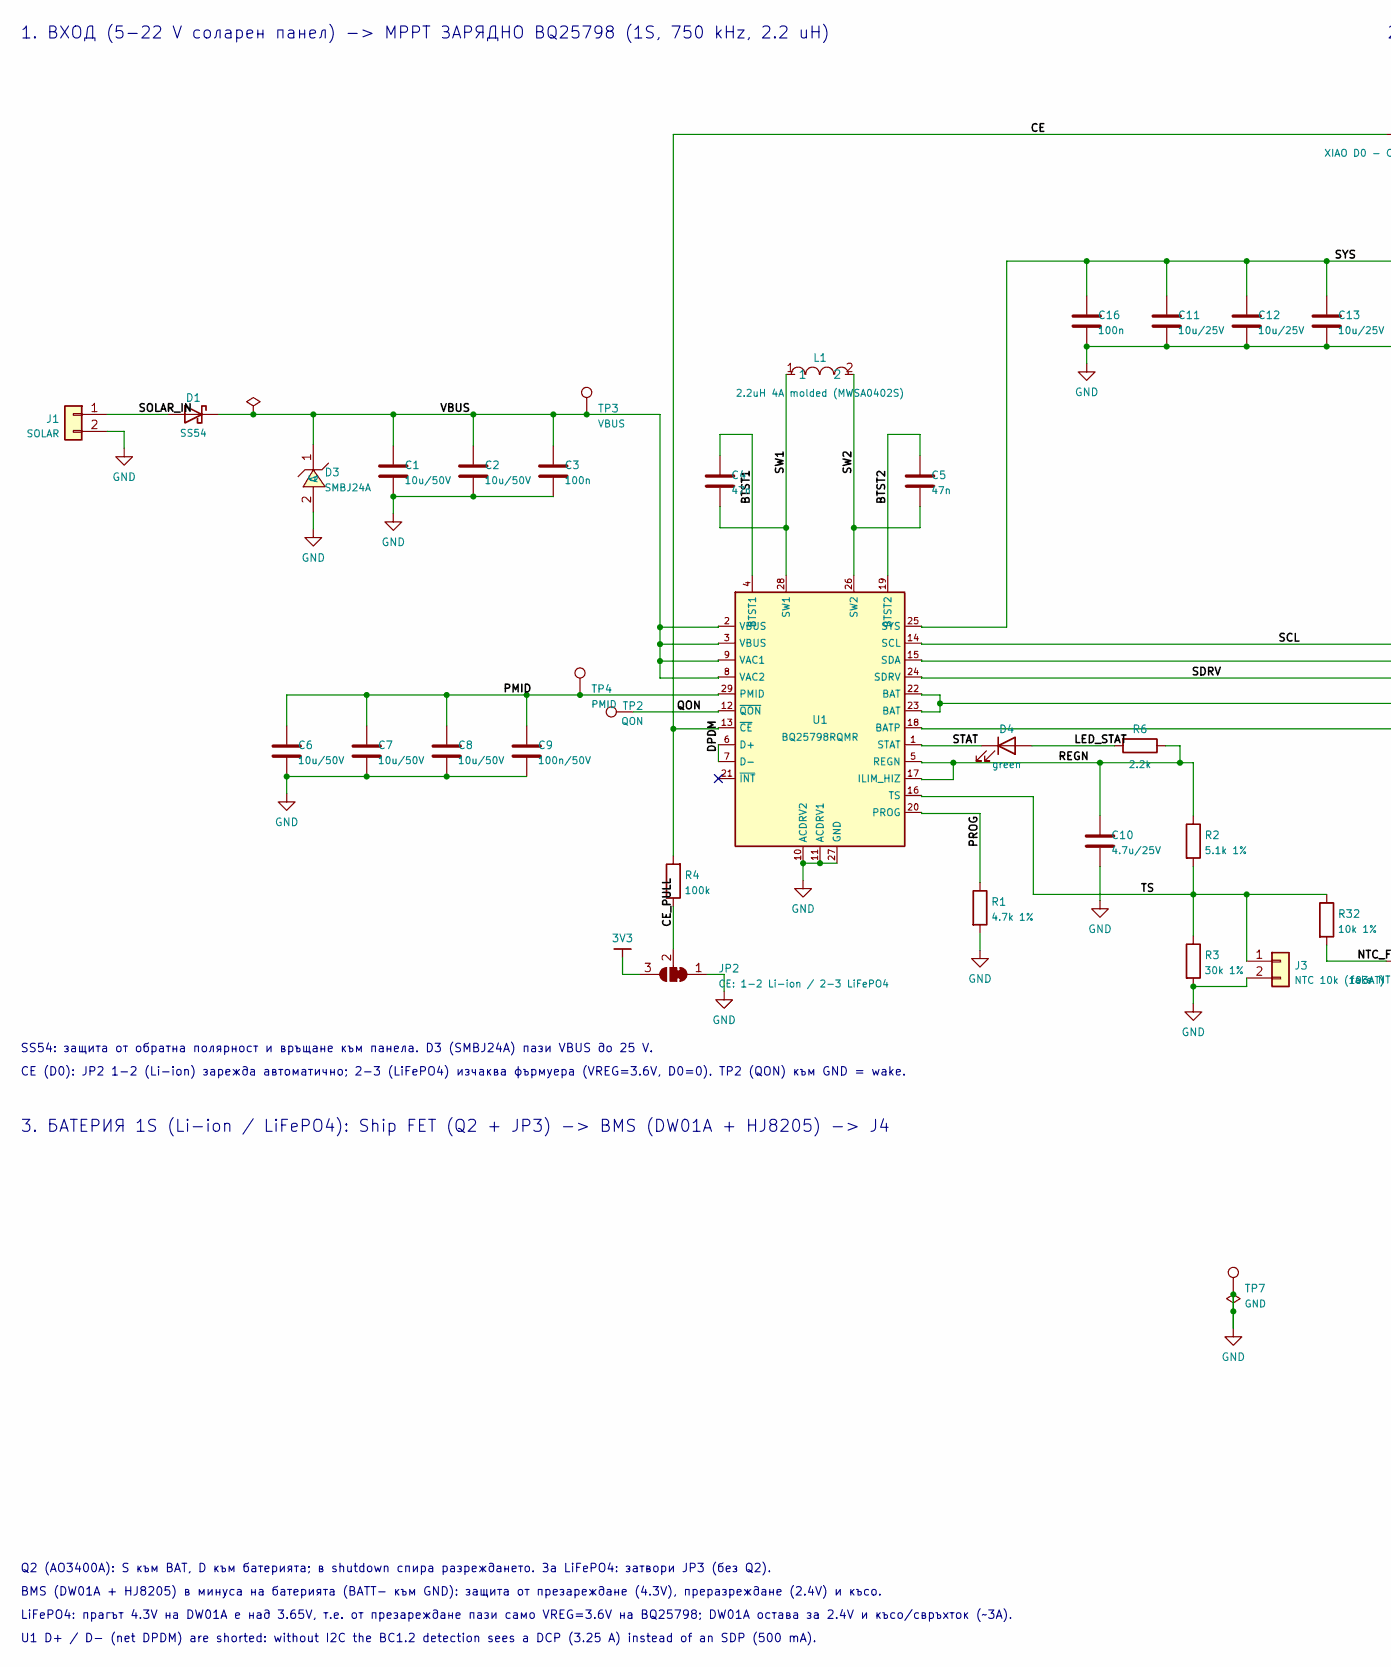
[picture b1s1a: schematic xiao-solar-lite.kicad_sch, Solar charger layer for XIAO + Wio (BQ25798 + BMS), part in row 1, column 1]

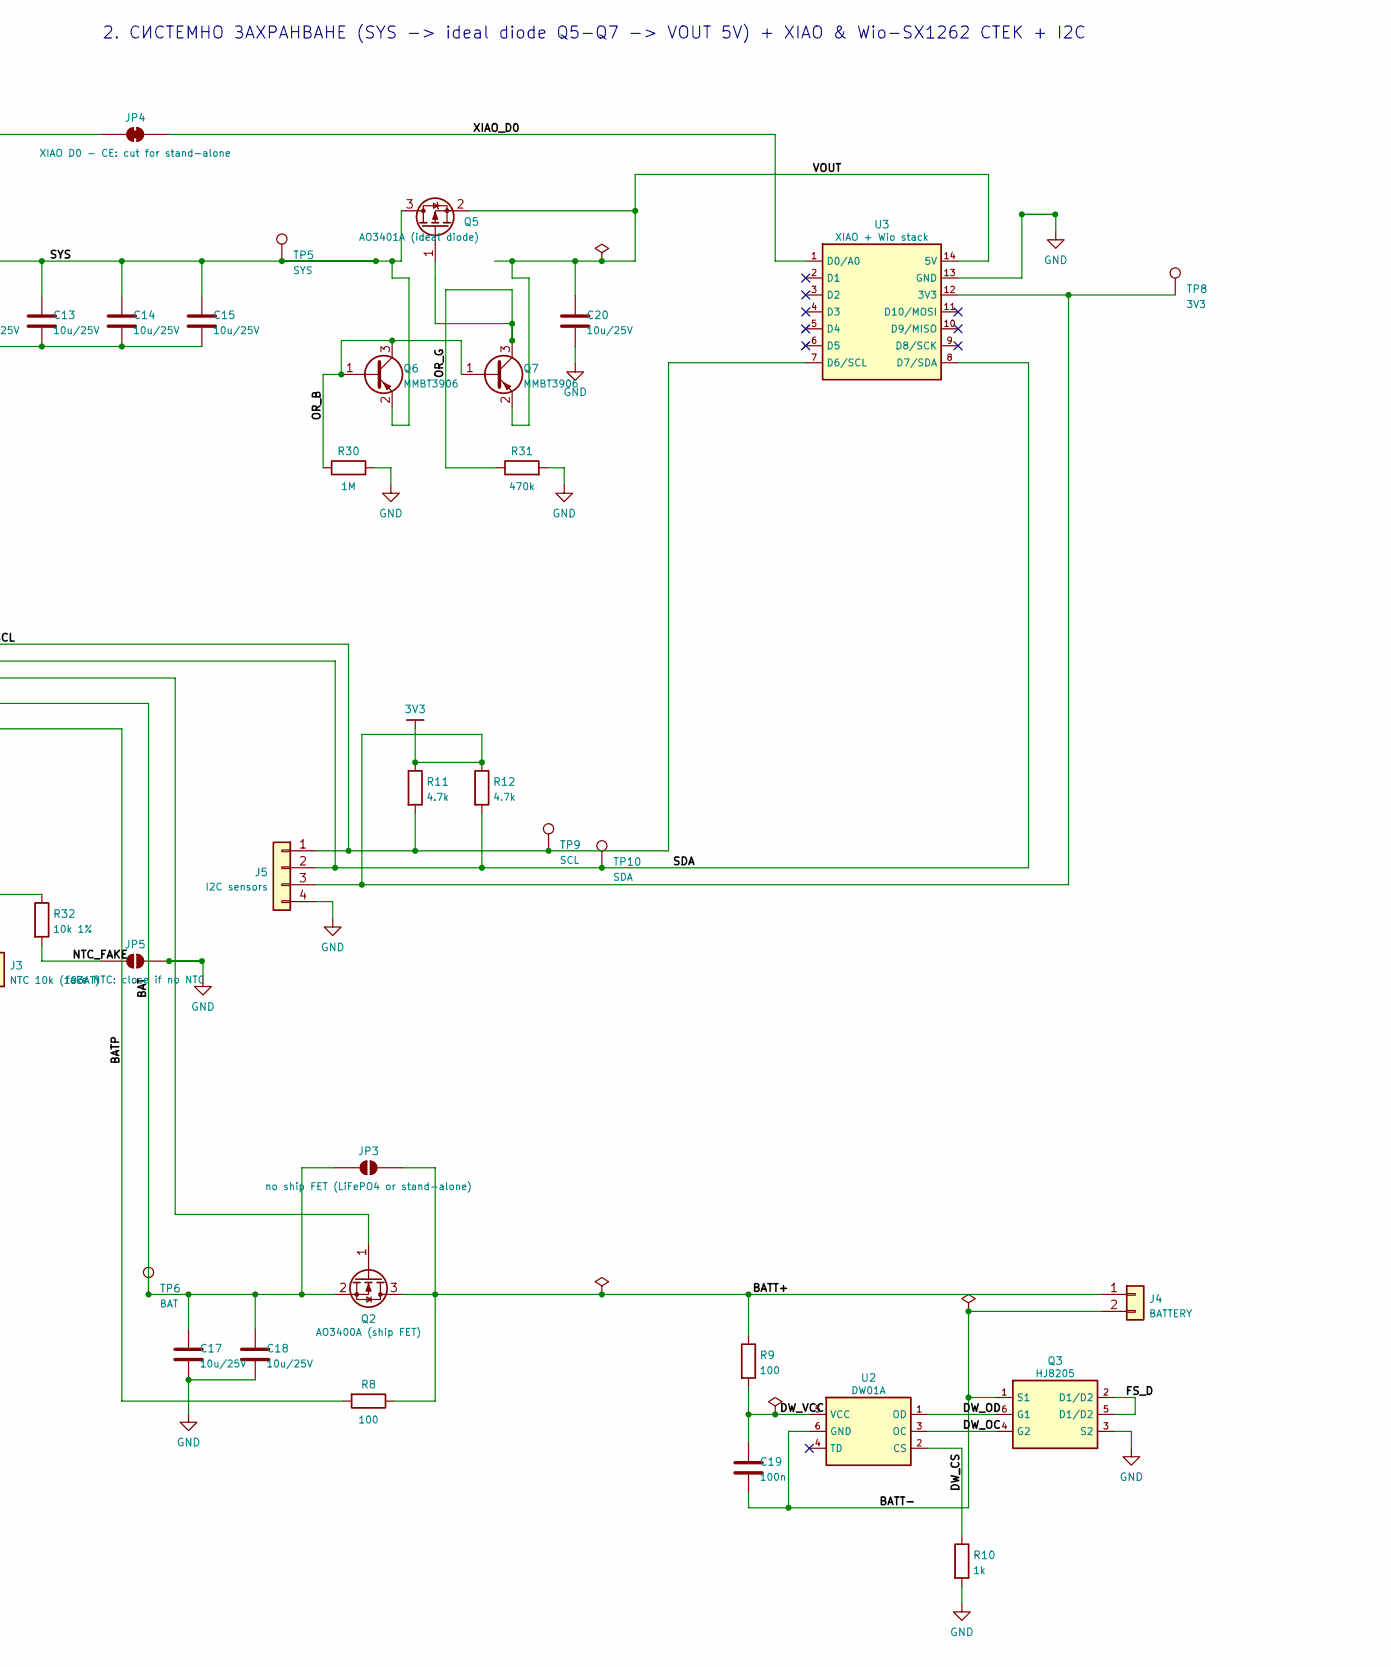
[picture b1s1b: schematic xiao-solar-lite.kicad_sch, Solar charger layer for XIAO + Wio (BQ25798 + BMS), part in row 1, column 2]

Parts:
C1, C2, C6, C7, C8: 10u/50V; C_1206_3216Metric; LCSC C13585
C3, C19: 100n; C_0603_1608Metric; LCSC C14663
C4, C5: 47n; C_0603_1608Metric; LCSC C1622
C9: 100n/50V; C_0402_1005Metric; LCSC C307331
C10: 4.7u/25V; C_0805_2012Metric; LCSC C1779
C11, C12, C13, C14, C15, C17, C18, C20: 10u/25V; C_0805_2012Metric; LCSC C15850
C16: 100n; C_0402_1005Metric; LCSC C1525
D1: SS54; D_SMA; LCSC C22452
D3: SMBJ24A; SMB_L4.6-W3.6-LS5.3-RD; LCSC C19077578
D4: green; LED_0805_2012Metric; LCSC C2297
J1: SOLAR; PinHeader_1x02_P2.54mm_Vertical
J3: NTC 10k (103AT); PinHeader_1x02_P2.54mm_Vertical
J4: BATTERY; PinHeader_1x02_P2.54mm_Vertical
J5: I2C sensors; PinHeader_1x04_P2.54mm_Vertical
JP2: CE: 1-2 Li-ion / 2-3 LiFePO4; SolderJumper-3_P1.3mm_Bridged12_RoundedPad1.0x1.5mm
JP3: no ship FET (LiFePO4 or stand-alone); SolderJumper-2_P1.3mm_Open_RoundedPad1.0x1.5mm
JP4: XIAO D0 - CE: cut for stand-alone; SolderJumper-2_P1.3mm_Bridged_RoundedPad1.0x1.5mm
JP5: fake NTC: close if no NTC; SolderJumper-2_P1.3mm_Open_RoundedPad1.0x1.5mm
L1: 2.2uH 4A molded (MWSA0402S); IND-SMD_L4.4-W4.2_MWSA0402S; LCSC C408335
Q2: AO3400A (ship FET); SOT-23; LCSC C20917
Q3: HJ8205; SOT-23-6_L2.9-W1.6-P0.95-LS2.8-BL; LCSC C20069150
Q5: AO3401A (ideal diode); SOT-23; LCSC C15127
Q6, Q7: MMBT3906; SOT-23; LCSC C7420354
R1: 4.7k 1%; R_0603_1608Metric; LCSC C23162
R2: 5.1k 1%; R_0603_1608Metric; LCSC C23186
R3: 30k 1%; R_0603_1608Metric; LCSC C22984
R4: 100k; R_0603_1608Metric; LCSC C25803
R6: 2.2k; R_0603_1608Metric; LCSC C4190
R8, R9: 100; R_0603_1608Metric; LCSC C22775
R10: 1k; R_0603_1608Metric; LCSC C21190
R11, R12: 4.7k; R_0603_1608Metric; LCSC C23162
R30: 1M; R_0603_1608Metric; LCSC C22935
R31: 470k; R_0603_1608Metric; LCSC C23178
R32: 10k 1%; R_0402_1005Metric; LCSC C25744
TP2: QON; TestPoint_Pad_D1.0mm
TP3: VBUS; TestPoint_Pad_D1.0mm
TP4: PMID; TestPoint_Pad_D1.0mm
TP5: SYS; TestPoint_Pad_D1.0mm
TP6: BAT; TestPoint_Pad_D1.0mm
TP7: GND; TestPoint_Pad_D1.0mm
TP8: 3V3; TestPoint_Pad_D1.0mm
TP9: SCL; TestPoint_Pad_D1.0mm
TP10: SDA; TestPoint_Pad_D1.0mm
U1: BQ25798RQMR; QFN-29_L4.0-W4.0-P0.40-TL-BQ25792RQMR; LCSC C2876593
U2: DW01A; SOT-23-6_L2.9-W1.6-P0.95-LS2.8-BL; LCSC C351410
U3: XIAO + Wio stack; XIAO_14P_2.54_21x17.8mm

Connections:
3V3: J5.3, JP2.3 (B), R11.1, R12.1, TP8.1, U3.12 (3V3)
BAT: C17.1, C18.1, JP3.1 (A), Q2.2 (S), TP6.1, U1.22 (BAT), U1.23 (BAT)
BATP: R8.2, U1.18 (BATP)
BATT+: J4.1, JP3.2 (B), Q2.3 (D), R8.1, R9.1
BATT-: C19.2, J4.2, Q3.1 (S1), U2.6 (GND)
BTST1: C4.1, U1.4 (BTST1)
BTST2: C5.1, U1.19 (BTST2)
CE: JP4.2 (B), R4.2, U1.13 (~CE)
CE_PULL: JP2.2 (C), R4.1
DPDM: U1.6 (D+), U1.7 (D-)
DW_CS: R10.1, U2.2 (CS)
DW_OC: Q3.4 (G2), U2.3 (OC)
DW_OD: Q3.6 (G1), U2.1 (OD)
DW_VCC: C19.1, R9.2, U2.5 (VCC)
FS_D: Q3.2 (D1/D2), Q3.5 (D1/D2)
GND: C1.2, C2.2, C3.2, C6.2, C7.2, C8.2, C9.2, C10.2, C11.2, C12.2, C13.2, C14.2, C15.2, C16.2, C17.2, C18.2, C20.2, D3.2 (A), J1.2, J3.2, J5.4, JP2.1 (A), JP5.2 (B), Q3.3 (S2), R1.2, R3.2, R10.2, R30.2, R31.2, TP7.1, U1.10 (ACDRV2), U1.11 (ACDRV1), U1.27 (GND), U3.13 (GND)
LED_STAT: D4.2 (A), R6.2
NTC_FAKE: JP5.1 (A), R32.2
OR_B: Q6.1 (B), Q6.3 (C), Q7.1 (B), R30.1
OR_G: Q5.1 (G), Q7.3 (C), R31.1
PMID: C6.1, C7.1, C8.1, C9.1, TP4.1, U1.29 (PMID)
PROG: R1.1, U1.20 (PROG)
QON: TP2.1, U1.12 (~QON)
REGN: C10.1, R2.1, R6.1, U1.5 (REGN), U1.17 (ILIM_HIZ)
SCL: J5.1, R11.2, TP9.1, U1.14 (SCL), U3.7 (D6/SCL)
SDA: J5.2, R12.2, TP10.1, U1.15 (SDA), U3.8 (D7/SDA)
SDRV: Q2.1 (G), U1.24 (SDRV)
SOLAR_IN: D1.2 (A), J1.1
STAT: D4.1 (K), U1.1 (STAT)
SW1: C4.2, L1.1, U1.28 (SW1)
SW2: C5.2, L1.2, U1.26 (SW2)
SYS: C11.1, C12.1, C13.1, C14.1, C15.1, C16.1, Q5.3 (D), Q6.2 (E), TP5.1, U1.25 (SYS)
TS: J3.1, R2.2, R3.1, R32.1, U1.16 (TS)
VBUS: C1.1, C2.1, C3.1, D1.1 (K), D3.1 (C), TP3.1, U1.2 (VBUS), U1.3 (VBUS), U1.8 (VAC2), U1.9 (VAC1)
VOUT: C20.1, Q5.2 (S), Q7.2 (E), U3.14 (5V)
XIAO_D0: JP4.1 (A), U3.1 (D0/A0)

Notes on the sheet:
1. ВХОД (5-22 V соларен панел) -> MPPT ЗАРЯДНО BQ25798 (1S, 750 kHz, 2.2 uH)
SS54: защита от обратна полярност и връщане към панела. D3 (SMBJ24A) пази VBUS до 25 V.
CE (D0): JP2 1-2 (Li-ion) зарежда автоматично; 2-3 (LiFePO4) изчаква фърмуера (VREG=3.6V, D0=0). TP2 (QON) към GND = wake.
2. СИСТЕМНО ЗАХРАНВАНЕ (SYS -> ideal diode Q5-Q7 -> VOUT 5V) + XIAO & Wio-SX1262 СТЕК + I2C
3. БАТЕРИЯ 1S (Li-ion / LiFePO4): Ship FET (Q2 + JP3) -> BMS (DW01A + HJ8205) -> J4
Q2 (AO3400A): S към BAT, D към батерията; в shutdown спира разреждането. За LiFePO4: затвори JP3 (без Q2).
BMS (DW01A + HJ8205) в минуса на батерията (BATT- към GND): защита от презареждане (4.3V), преразреждане (2.4V) и късо.
LiFePO4: прагът 4.3V на DW01A е над 3.65V, т.е. от презареждане пази само VREG=3.6V на BQ25798; DW01A остава за 2.4V и късо/свръхток (~3A).
U1 D+ / D- (net DPDM) are shorted: without I2C the BC1.2 detection sees a DCP (3.25 A) instead of an SDP (500 mA).

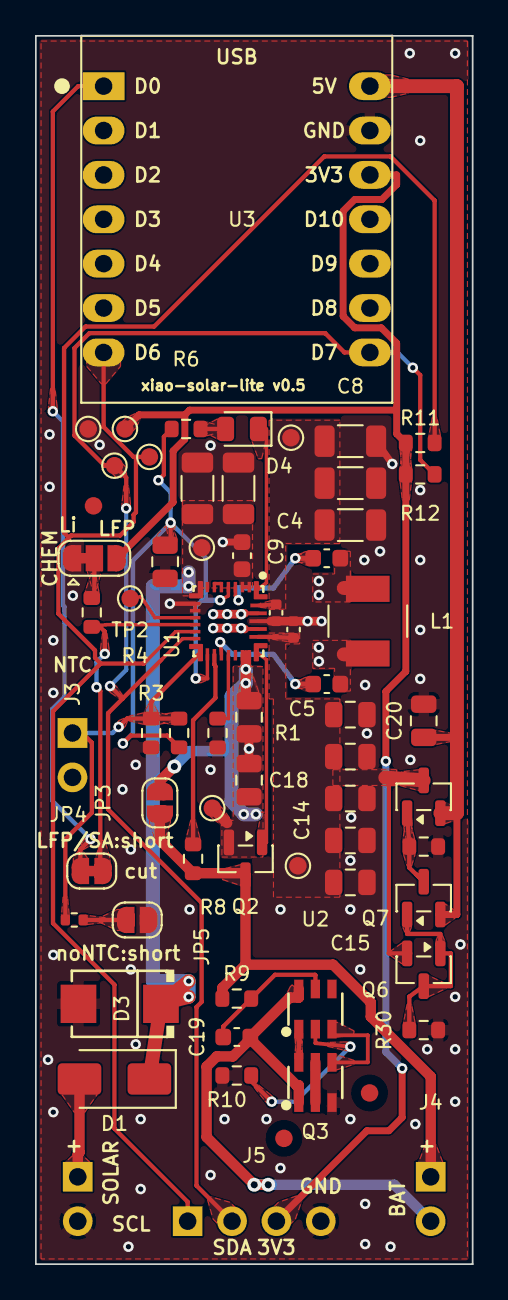
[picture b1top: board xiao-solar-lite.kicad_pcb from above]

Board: 2 copper layers, 25.0 x 70.3 mm, 65 parts (0 on the bottom side), 36 nets.

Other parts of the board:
FID1, FID2, FID3: Fiducial; Fiducial_1mm_Mask2mm

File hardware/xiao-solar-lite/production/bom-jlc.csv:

Comment,Designator,Footprint,LCSC
10u/50V,"C1,C2,C6,C7,C8",C_1206_3216Metric,C13585
4.7u/25V,C10,C_0805_2012Metric,C1779
10u/25V,"C11,C12,C13,C14,C15,C17,C18,C20",C_0805_2012Metric,C15850
100n,C16,C_0402_1005Metric,C1525
100n,"C3,C19",C_0603_1608Metric,C14663
47n,"C4,C5",C_0603_1608Metric,C1622
100n/50V,C9,C_0402_1005Metric,C307331
SS54,D1,D_SMA,C22452
SMBJ24A,D3,SMB_L4.6-W3.6-LS5.3-RD,C19077578
green,D4,LED_0805_2012Metric,C2297
2.2uH 4A molded (MWSA0402S),L1,IND-SMD_L4.4-W4.2_MWSA0402S,C408335
AO3400A (ship FET),Q2,SOT-23,C20917
HJ8205,Q3,SOT-23-6_L2.9-W1.6-P0.95-LS2.8-BL,C20069150
AO3401A (ideal diode),Q5,SOT-23,C15127
MMBT3906,"Q6,Q7",SOT-23,C7420354
4.7k 1%,"R1,R11,R12",R_0603_1608Metric,C23162
1k,R10,R_0603_1608Metric,C21190
5.1k 1%,R2,R_0603_1608Metric,C23186
30k 1%,R3,R_0603_1608Metric,C22984
1M,R30,R_0603_1608Metric,C22935
470k,R31,R_0603_1608Metric,C23178
10k 1%,R32,R_0402_1005Metric,C25744
100k,R4,R_0603_1608Metric,C25803
2.2k,R6,R_0603_1608Metric,C4190
100,"R8,R9",R_0603_1608Metric,C22775
BQ25798RQMR,U1,QFN-29_L4.0-W4.0-P0.40-TL-BQ25792RQMR,C2876593
DW01A,U2,SOT-23-6_L2.9-W1.6-P0.95-LS2.8-BL,C351410

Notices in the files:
README.md:
📜 License:
MeshCore is open-source software released under the MIT License. You are free to use, modify, and distribute it for personal and commercial projects.
